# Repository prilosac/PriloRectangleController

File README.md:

# PriloRectangleController
A digital controller PCB/chassis design meant to be easy to order and assemble while remaining a professional feeling and relatively customizable product.

HEAVILY inspired by GCCMX from Crane1195, which this repository was forked from.

ToDo: Replace these images with images made from this repository's files (these are from Crane's original repo)

The PCB is design to allow easy surface mount soldering of a Raspberry Pi Pico, the preferred board for DIY rectangle controllers in the community currently. It is also designed to easily solder a [Model U](https://github.com/Crane1195/Model-U) to with headers.

Credit to RMZ Customs for the hand drawn Pico diagram, and Austin for the modified Pico kicad files (and for lots of help in general).

## Parts:
1. [2.54mm pitch low profile header](https://www.digikey.com/en/products/detail/samtec-inc/TLW-136-05-T-S/1105024) (allows for thinner rectangle. alternatively use regular (2.50mm insulatio height) headers and allow for an extra 0.98mm of clearance in the case)
2. [M6 size fastener bolts](https://www.amazon.com/gp/product/B07QF7VB9P/ref=ppx_yo_dt_b_asin_title_o00_s00?ie=UTF8&th=1)

## License
This project is licenced under the GNU GPL Version 3. [See the included LICENSE file for details](LICENSE).

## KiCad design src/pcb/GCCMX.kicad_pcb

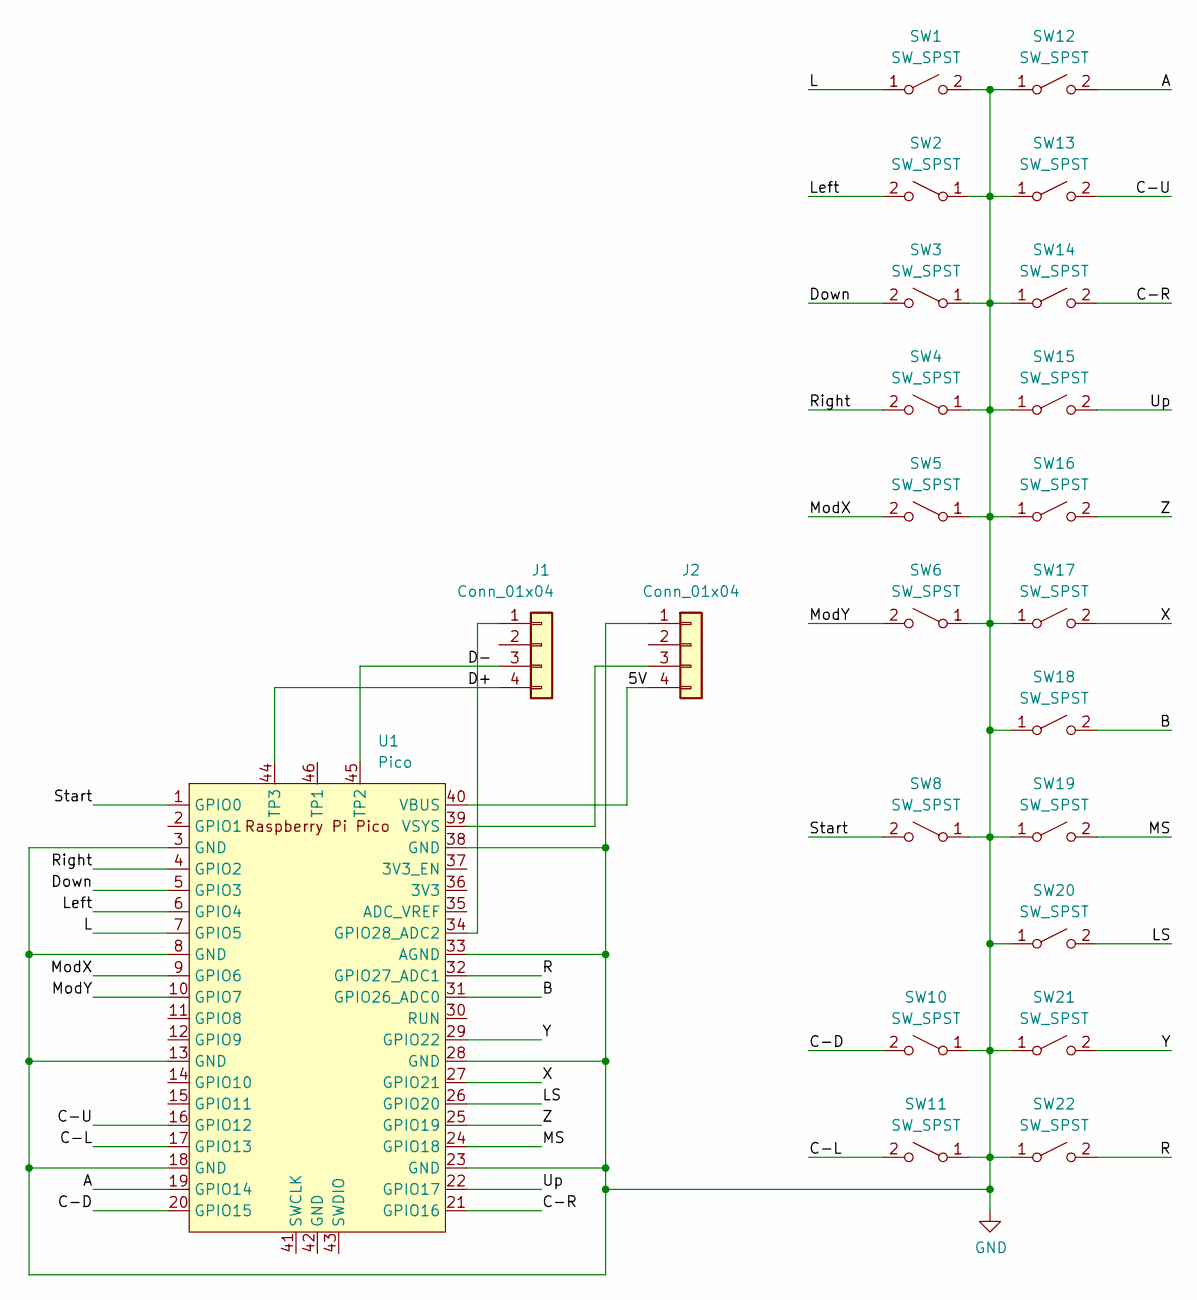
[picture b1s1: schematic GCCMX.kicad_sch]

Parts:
J1, J2: Conn_01x04; PinHeader_1x04_P2.54mm_Vertical
SW1, SW2, SW3, SW4, SW5, SW6, SW8, SW10, SW11, SW12, SW13, SW14, SW15, SW16, SW17, SW18, SW19, SW20, SW21, SW22: SW_SPST; Kailh_socket_MX+PG1350
U1: Pico; RPi_Pico_Removed3Pins

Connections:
/5V: J2.4, U1.40 (VBUS)
/A: SW12.2 (B), U1.19 (GPIO14)
/B: SW18.2 (B), U1.31 (GPIO26_ADC0)
/C-D: SW10.2 (B), U1.20 (GPIO15)
/C-L: SW11.2 (B), U1.17 (GPIO13)
/C-R: SW14.2 (B), U1.21 (GPIO16)
/C-U: SW13.2 (B), U1.16 (GPIO12)
/D+: J1.4, U1.44 (TP3)
/D-: J1.3, U1.45 (TP2)
/Down: SW3.2 (B), U1.5 (GPIO3)
/L: SW1.1 (A), U1.7 (GPIO5)
/LS: SW20.2 (B), U1.26 (GPIO20)
/Left: SW2.2 (B), U1.6 (GPIO4)
/MS: SW19.2 (B), U1.24 (GPIO18)
/ModX: SW5.2 (B), U1.9 (GPIO6)
/ModY: SW6.2 (B), U1.10 (GPIO7)
/R: SW22.2 (B), U1.32 (GPIO27_ADC1)
/Right: SW4.2 (B), U1.4 (GPIO2)
/Start: SW8.2 (B), U1.1 (GPIO0)
/Up: SW15.2 (B), U1.22 (GPIO17)
/X: SW17.2 (B), U1.27 (GPIO21)
/Y: SW21.2 (B), U1.29 (GPIO22)
/Z: SW16.2 (B), U1.25 (GPIO19)
GND: J2.1, SW1.2 (B), SW2.1 (A), SW3.1 (A), SW4.1 (A), SW5.1 (A), SW6.1 (A), SW8.1 (A), SW10.1 (A), SW11.1 (A), SW12.1 (A), SW13.1 (A), SW14.1 (A), SW15.1 (A), SW16.1 (A), SW17.1 (A), SW18.1 (A), SW19.1 (A), SW20.1 (A), SW21.1 (A), SW22.1 (A), U1.3 (GND), U1.8 (GND), U1.13 (GND), U1.18 (GND), U1.23 (GND), U1.28 (GND), U1.33 (AGND), U1.38 (GND)
unnamed: J1.1, U1.34 (GPIO28_ADC2)
unnamed: J2.3, U1.39 (VSYS)

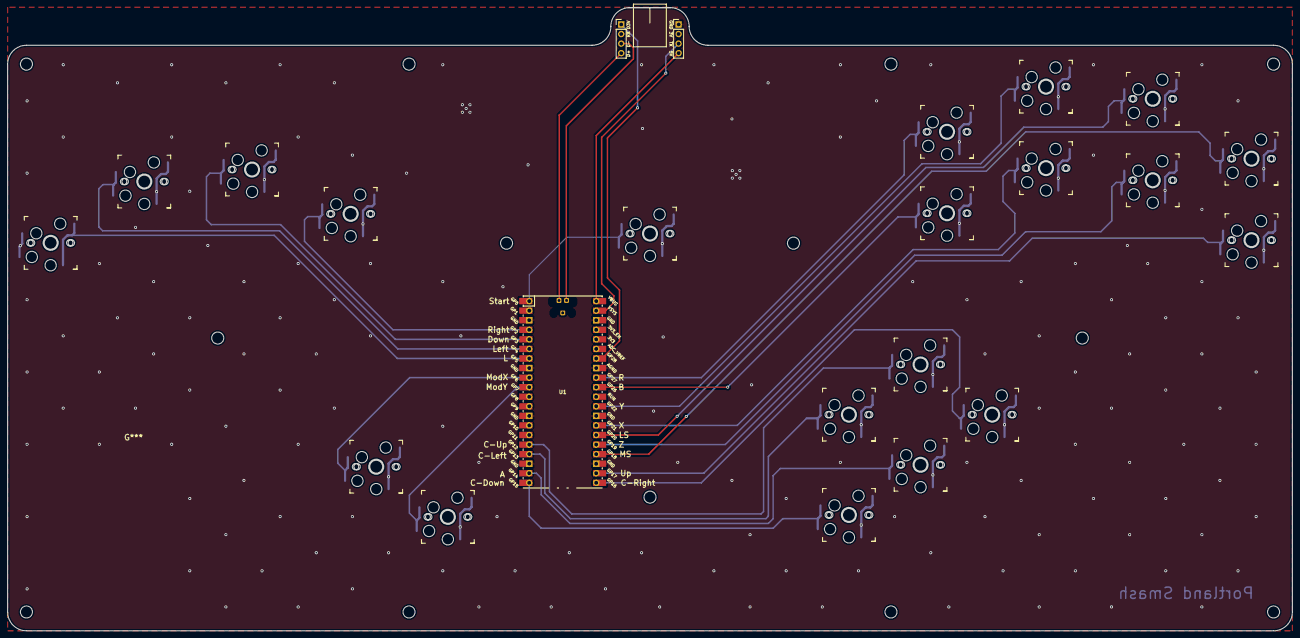
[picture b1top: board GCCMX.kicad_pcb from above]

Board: 2 copper layers, 341.2 x 165.5 mm, 23 parts (0 on the bottom side), 26 nets.

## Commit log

2022-05-17 pushing everything up from prior work
2022-06-26 updated wall layers and usbc for a bit more support
2022-08-06 updated pcb, moved USB to front so we no longer require a separate passthrough cable
2022-08-06 reduced overall size of case by 20mm horizontally and 8mm vertically, adjusted fastener bolt holes in accordance.
2022-11-01 looots of case updates. just need to flip the model UD from the back to the front and im ready to test v3 i think
2022-11-02 updated PCB to have model UD on top, regenerated fab files
